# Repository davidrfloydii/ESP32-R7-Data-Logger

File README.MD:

# NOTE THIS PROJECT WILL BE ABANDONED GIVEN THE LIMITATIONS OF THE ESP32-WROOM-32 SD SPEEDS. A NEW PROJECT WILL BE ADDED THAT USES THE ESP32P4

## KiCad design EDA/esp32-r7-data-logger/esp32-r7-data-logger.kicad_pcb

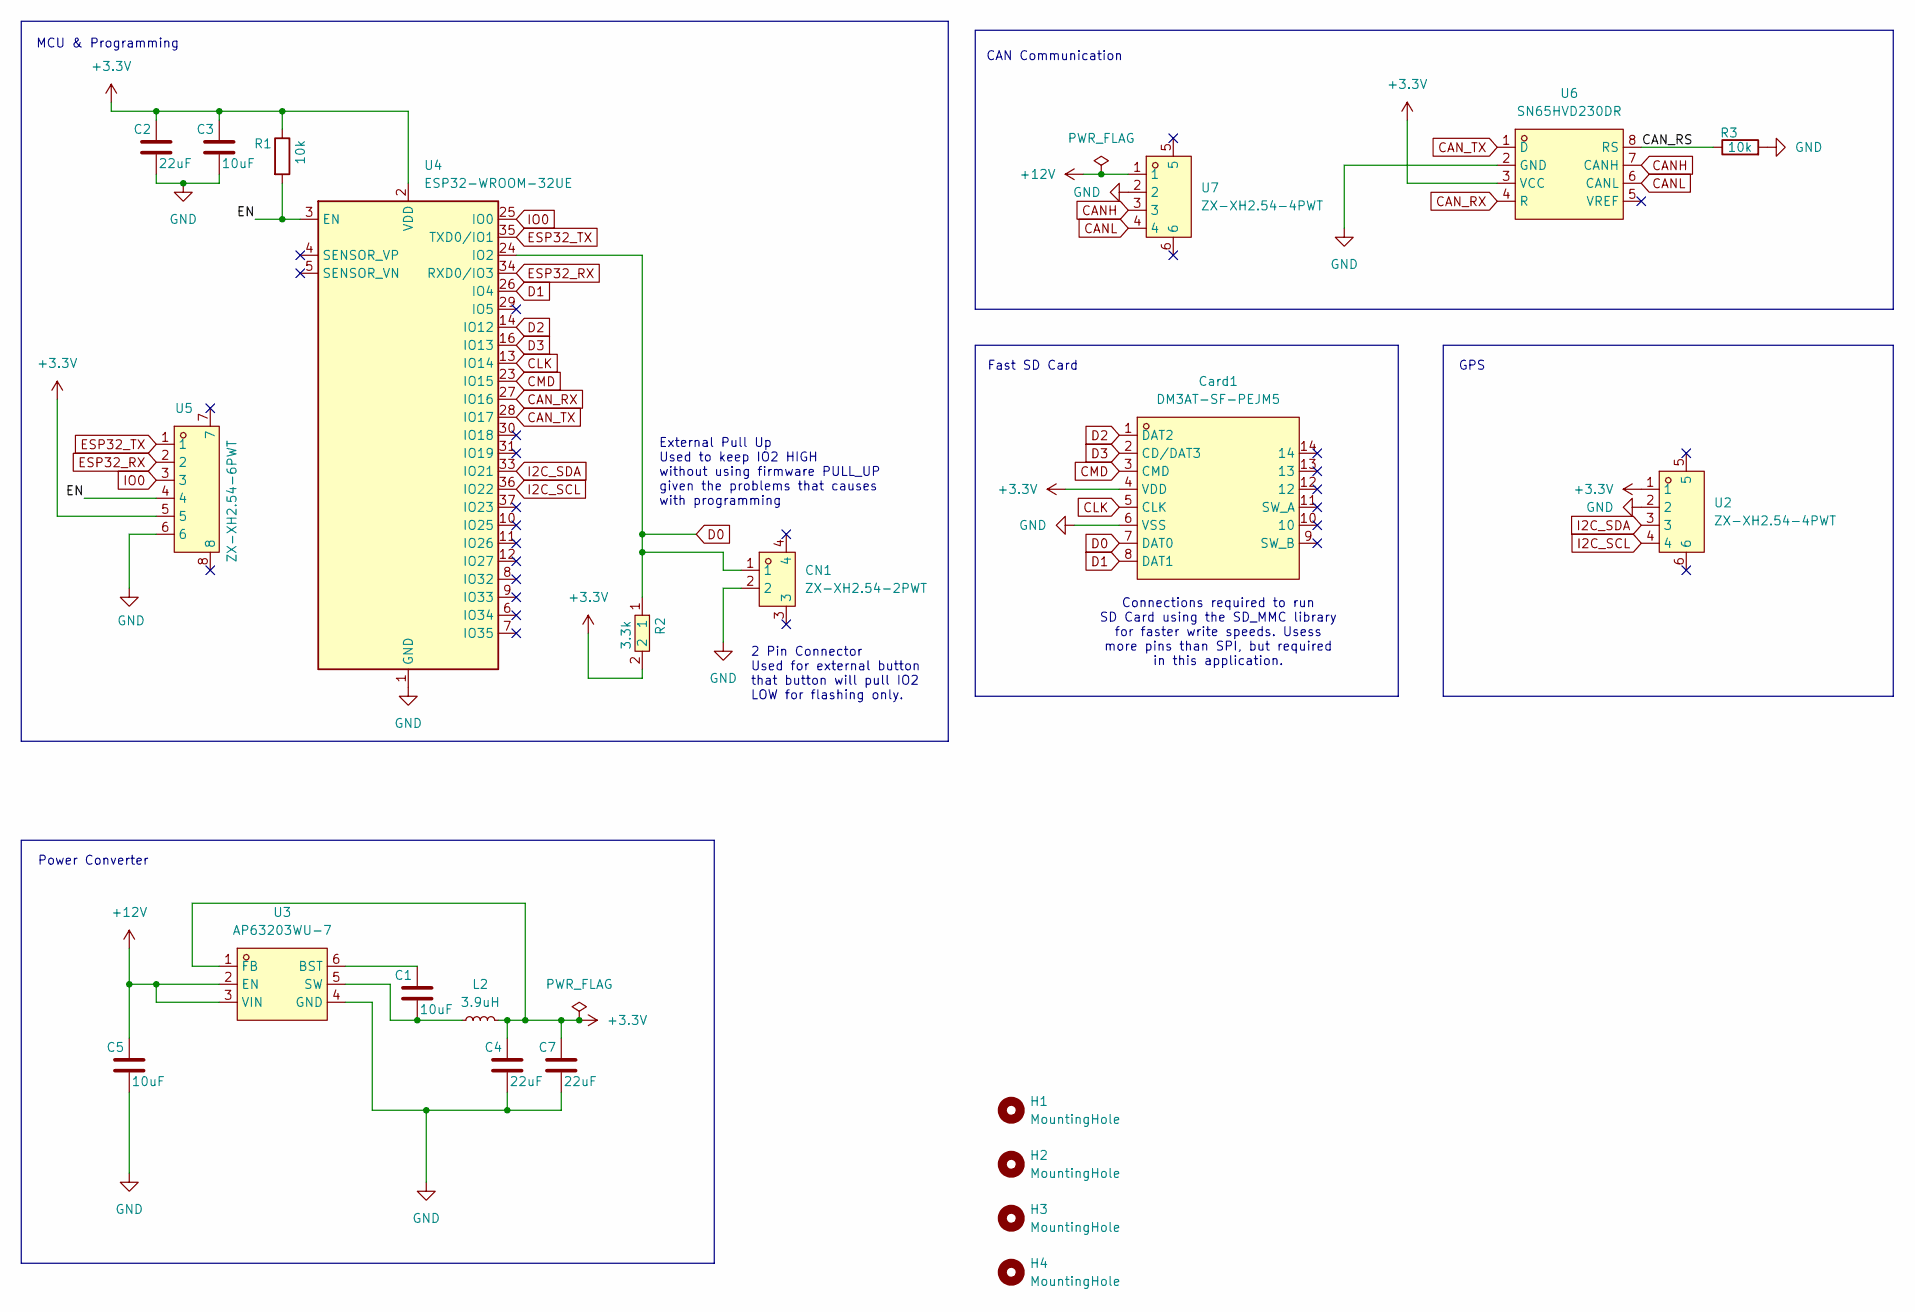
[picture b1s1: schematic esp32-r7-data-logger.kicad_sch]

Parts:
C1, C3, C5: 10uF; C1206; LCSC Part C24497
C2, C4, C7: 22uF; C1206; LCSC Part C87996
CN1: ZX-XH2.54-2PWT; CONN-SMD_2P-P2.54_MEGASTAR_ZX-XH2.54-2PWT; LCSC Part C7429671
Card1: DM3AT-SF-PEJM5; SD-SMD_DM3AT-SF-PEJM5; LCSC Part C114218
H1, H2, H3, H4: MountingHole; MountingHole_2.5mm
L2: 3.9uH; L1210; LCSC Part C295120
R1, R3: 10k; R1206; LCSC Part C17902
R2: 3.3k; R1206; LCSC Part C26032
U2, U7: ZX-XH2.54-4PWT; CONN-SMD_4P-P2.50-WAFER-254W-4P; LCSC Part C7429673
U3: AP63203WU-7; TSOT-26_L2.9-W1.6-P0.95-LS2.8-BL; LCSC Part C780769
U4: ESP32-WROOM-32UE; WIFIM-SMD_38P-L19.2-W18.0-P1.27; LCSC Part C328062
U5: ZX-XH2.54-6PWT; CONN-SMD_ZX-XH2.54-6PWT; LCSC Part C7429675
U6: SN65HVD230DR; SOIC-8_L4.9-W3.9-P1.27-LS6.0-BL; LCSC Part C12084

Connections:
+3.3V: C2.1, C3.1, C4.1, C7.1, Card1.4 (VDD), L2.2, R1.1, R2.2, U2.1, U3.1 (FB), U4.2 (VDD), U5.5, U6.3 (VCC)
+12V: C5.1, U3.2 (EN), U3.3 (VIN), U7.1; also elsewhere on the board
/CAN_RS: R3.1, U6.8 (RS)
/EN: R1.2, U4.3 (EN), U5.4
CANH: U6.7 (CANH), U7.3
CANL: U6.6 (CANL), U7.4
CAN_RX: U4.27 (IO16), U6.4 (R)
CAN_TX: U4.28 (IO17), U6.1 (D)
CLK: Card1.5 (CLK), U4.13 (IO14)
CMD: Card1.3 (CMD), U4.23 (IO15)
D0: CN1.1, Card1.7 (DAT0), R2.1, U4.24 (IO2)
D1: Card1.8 (DAT1), U4.26 (IO4)
D2: Card1.1 (DAT2), U4.14 (IO12)
D3: Card1.2 (CD/DAT3), U4.16 (IO13)
ESP32_RX: U4.34 (RXD0/IO3), U5.2
ESP32_TX: U4.35 (TXD0/IO1), U5.1
GND: C2.2, C3.2, C4.2, C5.2, C7.2, CN1.2, Card1.6 (VSS), R3.2, U2.2, U3.4 (GND), U4.1 (GND), U4.15 (GND), U4.38 (GND), U4.39 (GND), U5.6, U6.2 (GND), U7.2; also elsewhere on the board
I2C_SCL: U2.4, U4.36 (IO22)
I2C_SDA: U2.3, U4.33 (IO21)
IO0: U4.25 (IO0), U5.3
unnamed: C1.1, U3.6 (BST)
unnamed: C1.2, L2.1, U3.5 (SW)

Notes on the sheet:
Fast SD Card
Connections required to run SD Card using the SD_MMC library for faster write speeds. Usess more pins than SPI, but required in this application.
CAN Communication
MCU & Programming
GPS
External Pull Up Used to keep IO2 HIGH without using firmware PULL_UP given the problems that causes with programming
2 Pin Connector Used for external button that button will pull IO2 LOW for flashing only.
Power Converter

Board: 2 copper layers, 23 parts (0 on the bottom side), 22 nets, no tracks yet.

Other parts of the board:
C9: 100nF; C1206

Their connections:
+12V: C9.1; also elsewhere on the board
GND: C9.2; also elsewhere on the board

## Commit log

2025-12-09 Starting project with sample sparkfun code that gets 25Hz GNSS
2025-12-09 Adding shell for readme
2025-12-09 Cleanup of code still getting 25Hz
2025-12-09 Mode working structure built for SD card helper.
2025-12-09 Work started on SD card
2025-12-09 Basic SD writing is working
2025-12-09 Basic functionality of writing logs is working. However stuck at 15 data points per second.
2025-12-09 Updated data fields, removed scaling, and cleaned up code
2025-12-09 Fixed bug with not writing to SD when DEBUG was off
2025-12-09 Abandoning project for different MCU and codebase
2025-12-10 ESP32P4 working, still slow writes though
2025-12-10 ESP32 WROOM using SD_MMC which is capable of writing fast enough, however a bottleneck still exists.
2025-12-10 Updates to EDA files for symbols that don't throw errors during ERC
